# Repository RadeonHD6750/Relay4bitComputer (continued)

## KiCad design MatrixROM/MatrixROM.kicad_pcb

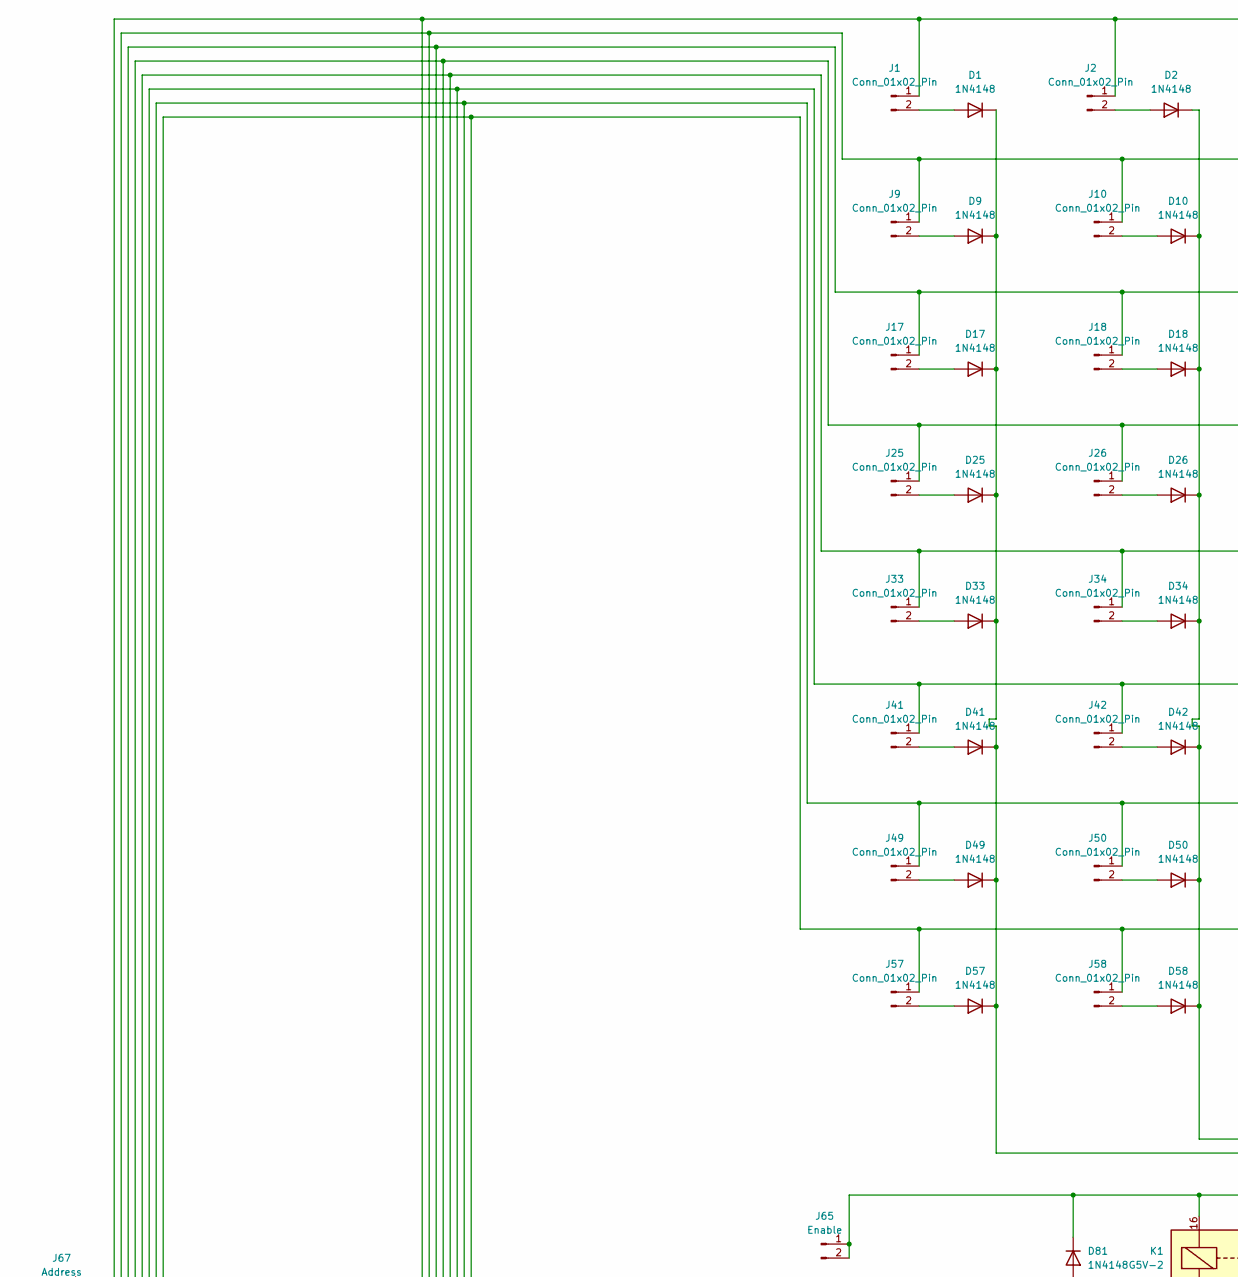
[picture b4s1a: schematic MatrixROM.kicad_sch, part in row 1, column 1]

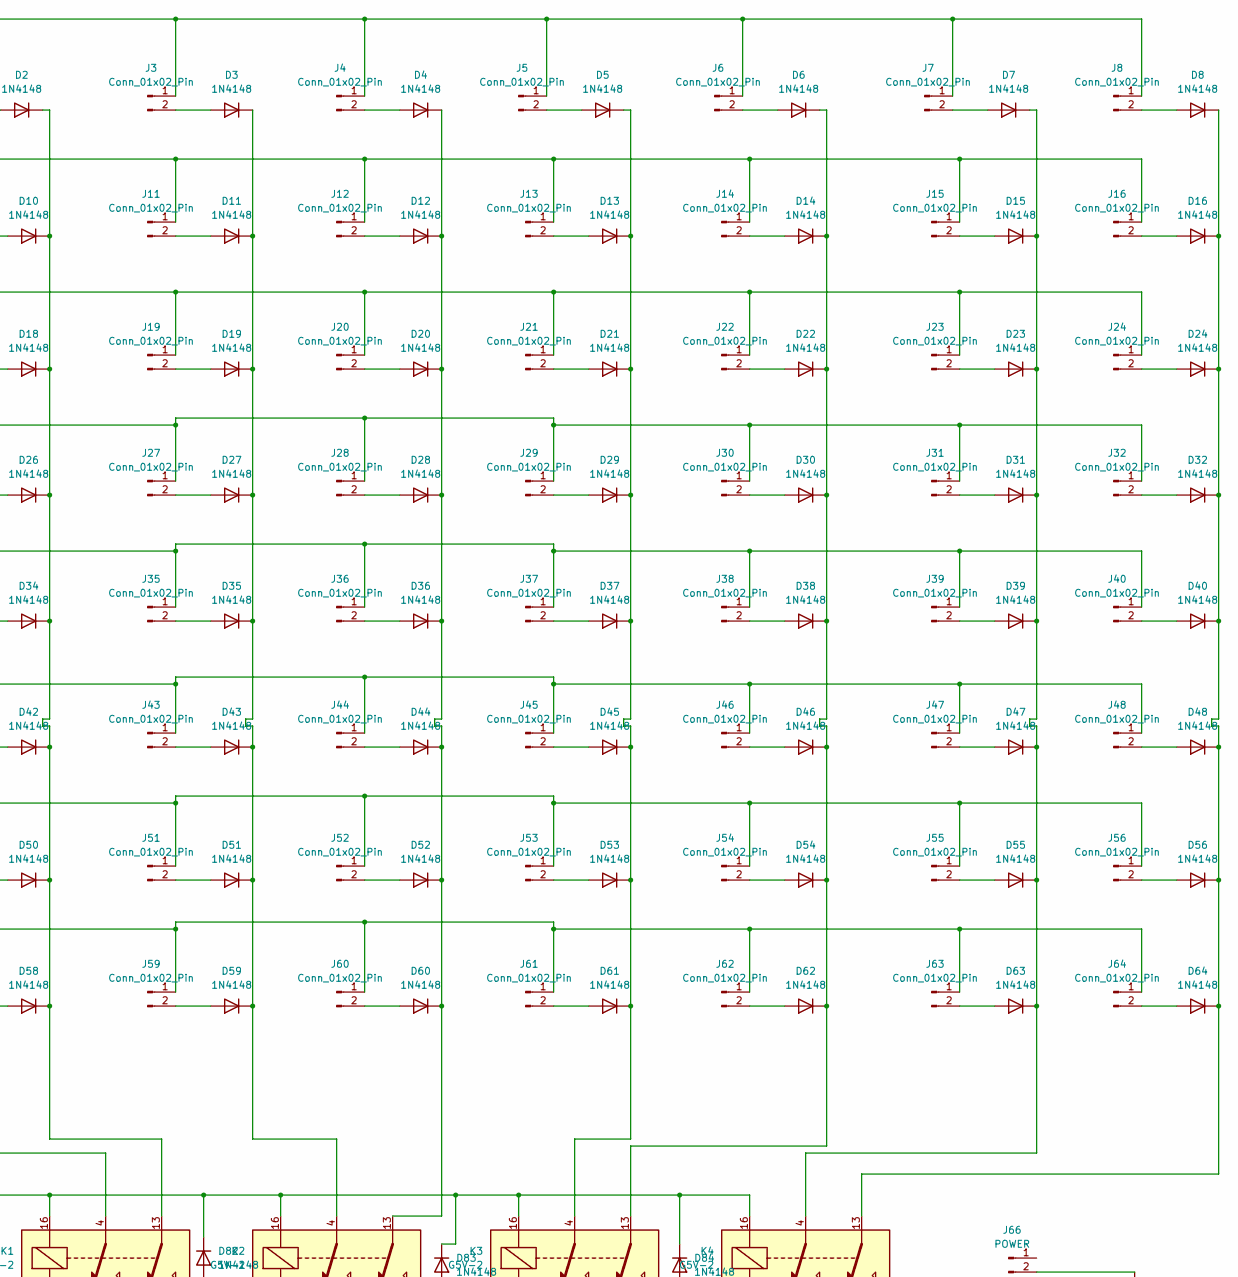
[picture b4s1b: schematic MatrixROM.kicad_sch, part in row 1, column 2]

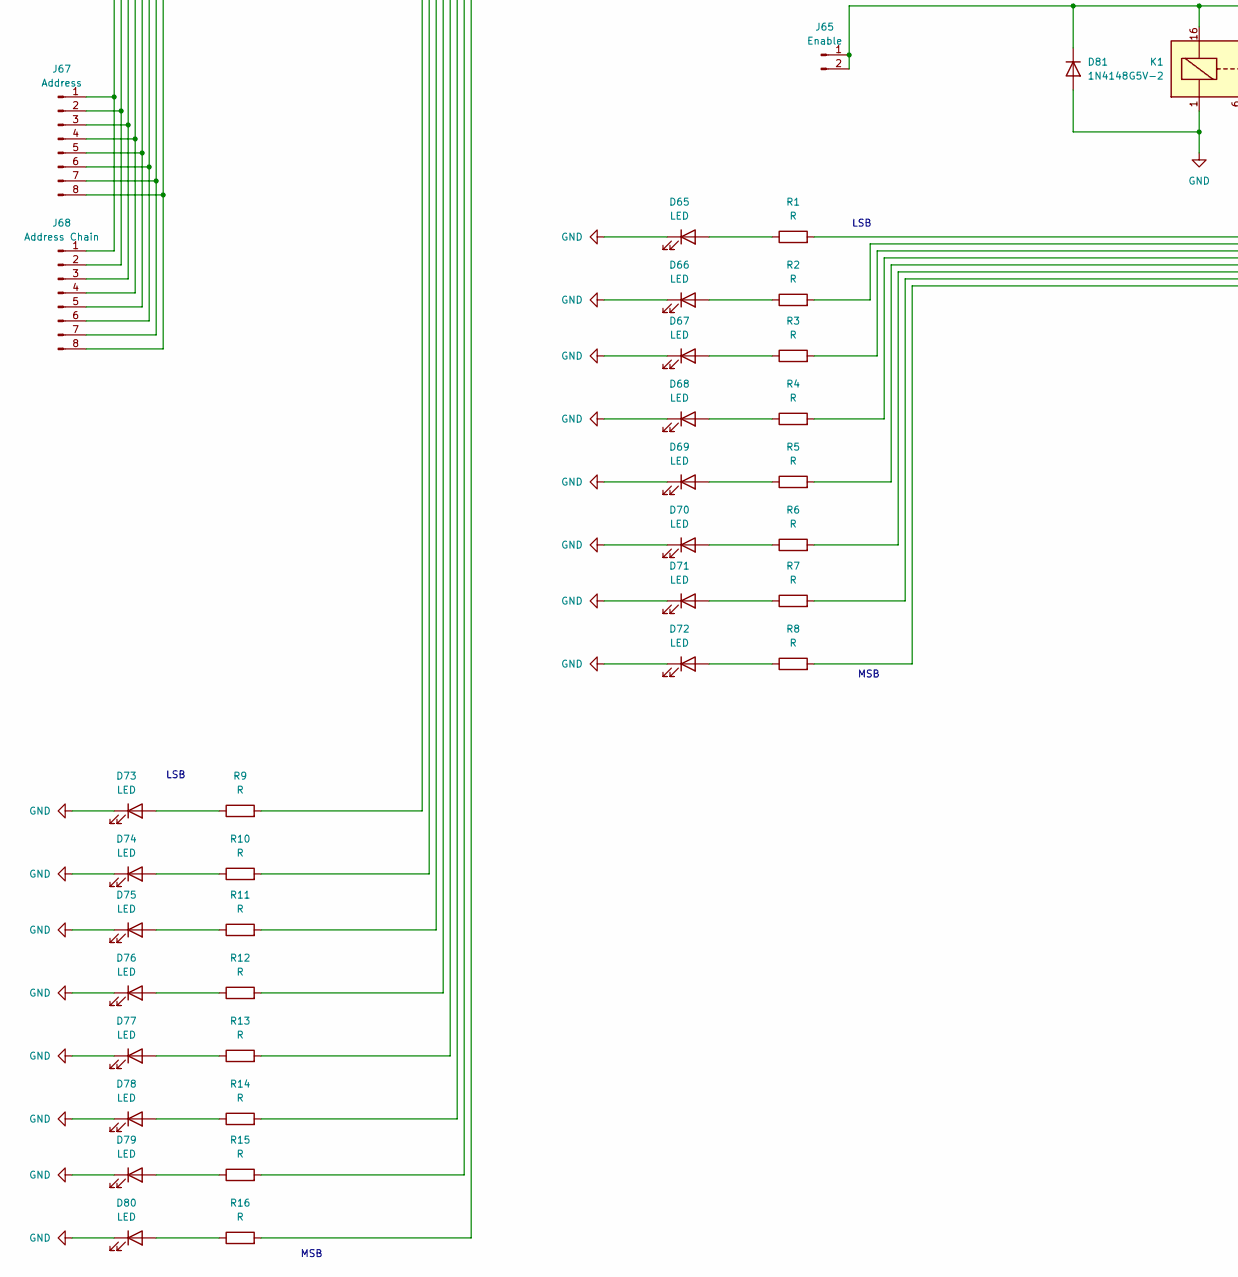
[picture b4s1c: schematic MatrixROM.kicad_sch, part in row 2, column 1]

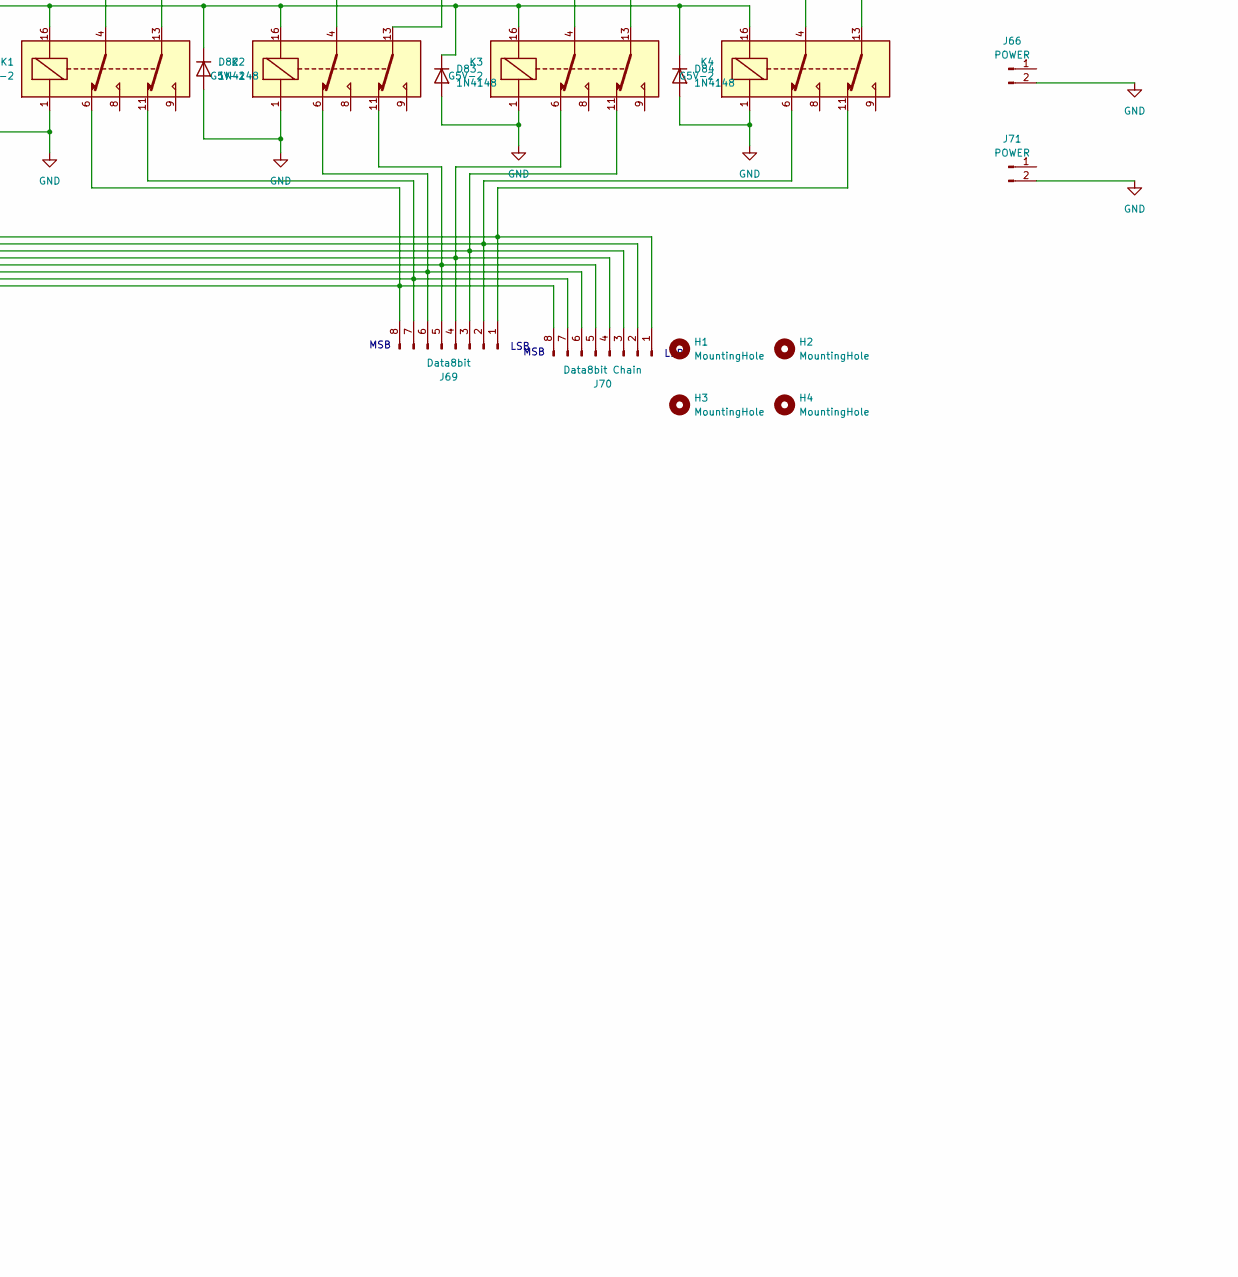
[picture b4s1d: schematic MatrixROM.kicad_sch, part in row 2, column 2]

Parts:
D1, D2, D3, D4, D5, D6, D7, D8, D9, D10, D11, D12, D13, D14, D15, D16, D17, D18, D19, D20, D21, D22, D23, D24, D25, D26, D27, D28, D29, D30, D31, D32, D33, D34, D35, D36, D37, D38, D39, D40, D41, D42, D43, D44, D45, D46, D47, D48, D49, D50, D51, D52, D53, D54, D55, D56, D57, D58, D59, D60, D61, D62, D63, D64, D81, D82, D83, D84: 1N4148; D_DO-35_SOD27_P7.62mm_Horizontal
D65, D66, D67, D68, D69, D70, D71, D72, D73, D74, D75, D76, D77, D78, D79, D80: LED; LED_D5.0mm
H1, H2, H3, H4: MountingHole; MountingHole_3.2mm_M3_Pad
J1, J2, J3, J4, J5, J6, J7, J8, J9, J10, J11, J12, J13, J14, J15, J16, J17, J18, J19, J20, J21, J22, J23, J24, J25, J26, J27, J28, J29, J30, J31, J32, J33, J34, J35, J36, J37, J38, J39, J40, J41, J42, J43, J44, J45, J46, J47, J48, J49, J50, J51, J52, J53, J54, J55, J56, J57, J58, J59, J60, J61, J62, J63, J64: Conn_01x02_Pin; PinHeader_1x02_P2.54mm_Vertical
J65: Enable; PinHeader_1x02_P2.54mm_Vertical
J66, J71: POWER; PinHeader_1x02_P2.54mm_Vertical
J67: Address; PinHeader_1x08_P2.54mm_Vertical
J68: Address Chain; PinHeader_1x08_P2.54mm_Vertical
J69: Data8bit; PinHeader_1x08_P2.54mm_Vertical
J70: Data8bit Chain; PinHeader_1x08_P2.54mm_Vertical
K1, K2, K3, K4: G5V-2; Relay_DPDT_Omron_G5V-2
R1, R2, R3, R4, R5, R6, R7, R8, R9, R10, R11, R12, R13, R14, R15, R16: R; R_Axial_DIN0207_L6.3mm_D2.5mm_P10.16mm_Horizontal

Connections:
GND: D65.1 (K), D66.1 (K), D67.1 (K), D68.1 (K), D69.1 (K), D70.1 (K), D71.1 (K), D72.1 (K), D73.1 (K), D74.1 (K), D75.1 (K), D76.1 (K), D77.1 (K), D78.1 (K), D79.1 (K), D80.1 (K), D81.2 (A), D82.2 (A), D83.2 (A), D84.2 (A), J66.2, J71.2, K1.1, K2.1, K3.1, K4.1
unnamed: D1.2 (A), J1.2
unnamed: D1.1 (K), D9.1 (K), D17.1 (K), D25.1 (K), D33.1 (K), D41.1 (K), D49.1 (K), D57.1 (K), K1.4
unnamed: D2.2 (A), J2.2
unnamed: D3.2 (A), J3.2
unnamed: D4.2 (A), J4.2
unnamed: D5.2 (A), J5.2
unnamed: D6.2 (A), J6.2
unnamed: D7.2 (A), J7.2
unnamed: D8.2 (A), J8.2
unnamed: D9.2 (A), J9.2
unnamed: D10.2 (A), J10.2
unnamed: D2.1 (K), D10.1 (K), D18.1 (K), D26.1 (K), D34.1 (K), D42.1 (K), D50.1 (K), D58.1 (K), K1.13
unnamed: D11.2 (A), J11.2
unnamed: D3.1 (K), D11.1 (K), D19.1 (K), D27.1 (K), D35.1 (K), D43.1 (K), D51.1 (K), D59.1 (K), K2.4
unnamed: D12.2 (A), J12.2
unnamed: D4.1 (K), D12.1 (K), D20.1 (K), D28.1 (K), D36.1 (K), D44.1 (K), D52.1 (K), D60.1 (K), K2.13
unnamed: D13.2 (A), J13.2
unnamed: D5.1 (K), D13.1 (K), D21.1 (K), D29.1 (K), D37.1 (K), D45.1 (K), D53.1 (K), D61.1 (K), K3.4
unnamed: D14.2 (A), J14.2
unnamed: D6.1 (K), D14.1 (K), D22.1 (K), D30.1 (K), D38.1 (K), D46.1 (K), D54.1 (K), D62.1 (K), K3.13
unnamed: D15.2 (A), J15.2
unnamed: D7.1 (K), D15.1 (K), D23.1 (K), D31.1 (K), D39.1 (K), D47.1 (K), D55.1 (K), D63.1 (K), K4.4
unnamed: D16.2 (A), J16.2
unnamed: D8.1 (K), D16.1 (K), D24.1 (K), D32.1 (K), D40.1 (K), D48.1 (K), D56.1 (K), D64.1 (K), K4.13
unnamed: D17.2 (A), J17.2
unnamed: D18.2 (A), J18.2
unnamed: D19.2 (A), J19.2
unnamed: D20.2 (A), J20.2
unnamed: D21.2 (A), J21.2
unnamed: D22.2 (A), J22.2
unnamed: D23.2 (A), J23.2
unnamed: D24.2 (A), J24.2
unnamed: D25.2 (A), J25.2
unnamed: D26.2 (A), J26.2
unnamed: D27.2 (A), J27.2
unnamed: D28.2 (A), J28.2
unnamed: D29.2 (A), J29.2
unnamed: D30.2 (A), J30.2
unnamed: D31.2 (A), J31.2
unnamed: D32.2 (A), J32.2
unnamed: D33.2 (A), J33.2
unnamed: D34.2 (A), J34.2
unnamed: D35.2 (A), J35.2
unnamed: D36.2 (A), J36.2
unnamed: D37.2 (A), J37.2
unnamed: D38.2 (A), J38.2
unnamed: D39.2 (A), J39.2
unnamed: D40.2 (A), J40.2
unnamed: D41.2 (A), J41.2
unnamed: D42.2 (A), J42.2
unnamed: D43.2 (A), J43.2
unnamed: D44.2 (A), J44.2
unnamed: D45.2 (A), J45.2
unnamed: D46.2 (A), J46.2
unnamed: D47.2 (A), J47.2
unnamed: D48.2 (A), J48.2
unnamed: D49.2 (A), J49.2
unnamed: D50.2 (A), J50.2
unnamed: D51.2 (A), J51.2
unnamed: D52.2 (A), J52.2
unnamed: D53.2 (A), J53.2
unnamed: D54.2 (A), J54.2
unnamed: D55.2 (A), J55.2
unnamed: D56.2 (A), J56.2
unnamed: D57.2 (A), J57.2
unnamed: D58.2 (A), J58.2
unnamed: D59.2 (A), J59.2
unnamed: D60.2 (A), J60.2
unnamed: D61.2 (A), J61.2
unnamed: D62.2 (A), J62.2
unnamed: D63.2 (A), J63.2
unnamed: D64.2 (A), J64.2
unnamed: D65.2 (A), R1.1
unnamed: D66.2 (A), R2.1
unnamed: D67.2 (A), R3.1
unnamed: D68.2 (A), R4.1
unnamed: D69.2 (A), R5.1
unnamed: D70.2 (A), R6.1
unnamed: D71.2 (A), R7.1
unnamed: D72.2 (A), R8.1
unnamed: D73.2 (A), R9.1
unnamed: D74.2 (A), R10.1
unnamed: D75.2 (A), R11.1
unnamed: D76.2 (A), R12.1
unnamed: D77.2 (A), R13.1
unnamed: D78.2 (A), R14.1
unnamed: D79.2 (A), R15.1
unnamed: D80.2 (A), R16.1
unnamed: D81.1 (K), D82.1 (K), D83.1 (K), D84.1 (K), J65.1, J65.2, K1.16, K2.16, K3.16, K4.16
unnamed: J1.1, J2.1, J3.1, J4.1, J5.1, J6.1, J7.1, J8.1, J67.1, J68.1, R9.2
unnamed: J9.1, J10.1, J11.1, J12.1, J13.1, J14.1, J15.1, J16.1, J67.2, J68.2, R10.2
unnamed: J17.1, J18.1, J19.1, J20.1, J21.1, J22.1, J23.1, J24.1, J67.3, J68.3, R11.2
unnamed: J25.1, J26.1, J27.1, J28.1, J29.1, J30.1, J31.1, J32.1, J67.4, J68.4, R12.2
unnamed: J33.1, J34.1, J35.1, J36.1, J37.1, J38.1, J39.1, J40.1, J67.5, J68.5, R13.2
unnamed: J41.1, J42.1, J43.1, J44.1, J45.1, J46.1, J47.1, J48.1, J67.6, J68.6, R14.2
unnamed: J49.1, J50.1, J51.1, J52.1, J53.1, J54.1, J55.1, J56.1, J67.7, J68.7, R15.2
unnamed: J57.1, J58.1, J59.1, J60.1, J61.1, J62.1, J63.1, J64.1, J67.8, J68.8, R16.2
unnamed: J69.1, J70.1, K4.11, R1.2
unnamed: J69.2, J70.2, K4.6, R2.2
unnamed: J69.3, J70.3, K3.11, R3.2
unnamed: J69.4, J70.4, K3.6, R4.2
unnamed: J69.5, J70.5, K2.11, R5.2
unnamed: J69.6, J70.6, K2.6, R6.2
unnamed: J69.7, J70.7, K1.11, R7.2
unnamed: J69.8, J70.8, K1.6, R8.2

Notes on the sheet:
MSB
LSB

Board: 2 copper layers, 179 parts (16 on the bottom side), 106 nets, no tracks yet.

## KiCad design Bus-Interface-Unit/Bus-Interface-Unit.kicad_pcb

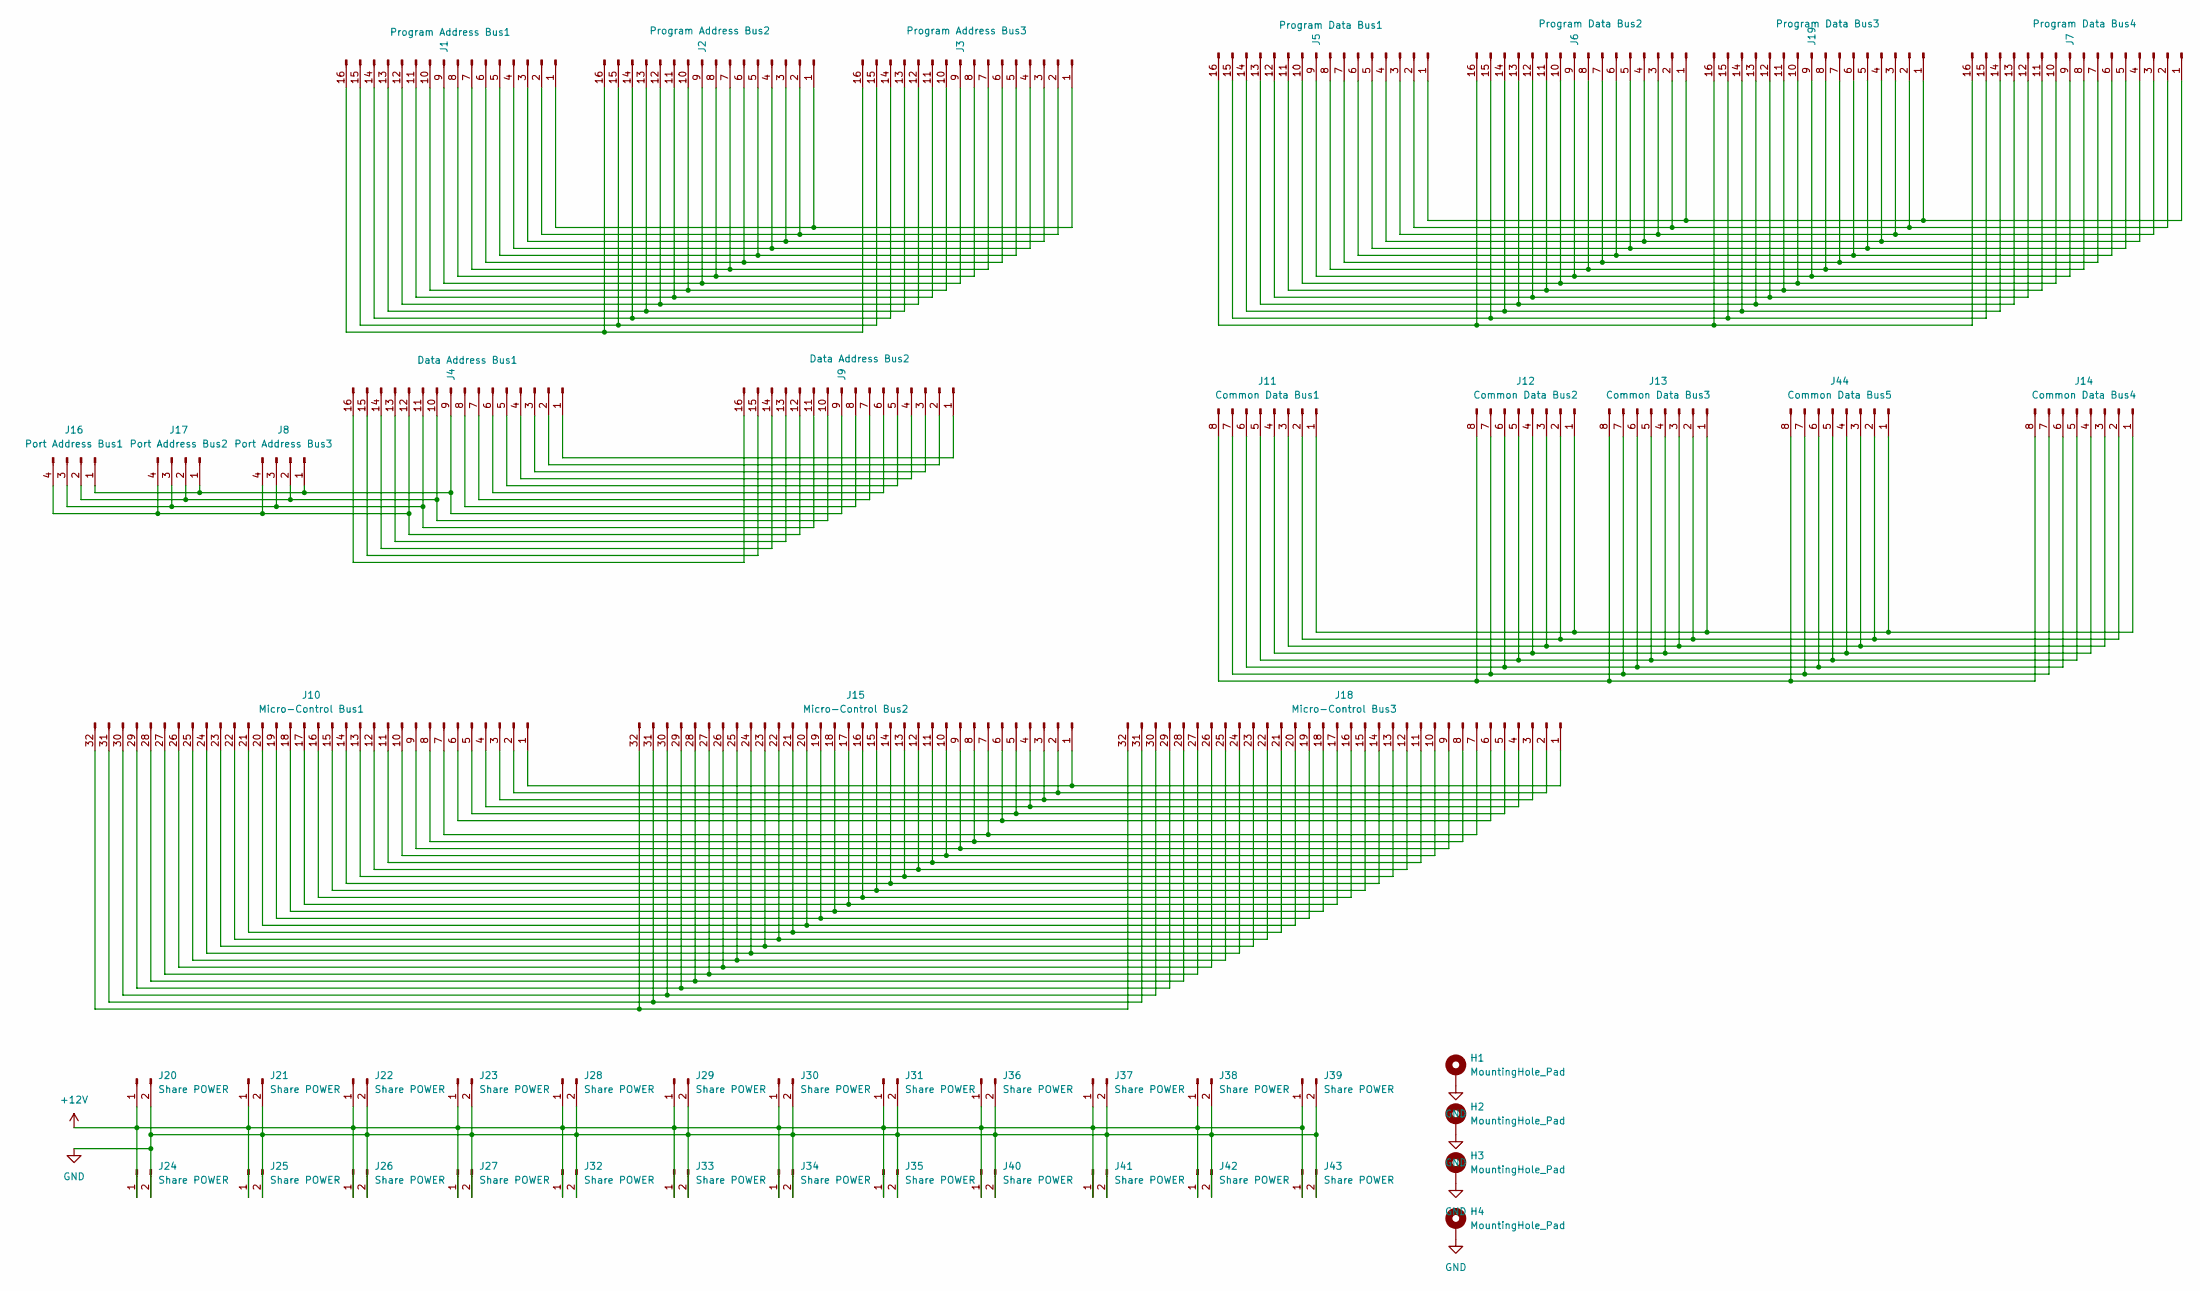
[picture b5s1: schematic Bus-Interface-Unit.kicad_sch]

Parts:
H1, H2, H3, H4: MountingHole_Pad; MountingHole_3.2mm_M3_Pad
J1: Program Address Bus1; PinHeader_1x16_P2.54mm_Vertical
J2: Program Address Bus2; PinHeader_1x16_P2.54mm_Vertical
J3: Program Address Bus3; PinHeader_1x16_P2.54mm_Vertical
J4: Data Address Bus1; PinHeader_1x16_P2.54mm_Vertical
J5: Program Data Bus1; PinHeader_1x16_P2.54mm_Vertical
J6: Program Data Bus2; PinHeader_1x16_P2.54mm_Vertical
J7: Program Data Bus4; PinHeader_1x16_P2.54mm_Vertical
J8: Port Address Bus3; PinHeader_1x04_P2.54mm_Vertical
J9: Data Address Bus2; PinHeader_1x16_P2.54mm_Vertical
J10: Micro-Control Bus1; PinHeader_1x32_P2.54mm_Vertical
J11: Common Data Bus1; PinHeader_1x08_P2.54mm_Vertical
J12: Common Data Bus2; PinHeader_1x08_P2.54mm_Vertical
J13: Common Data Bus3; PinHeader_1x08_P2.54mm_Vertical
J14: Common Data Bus4; PinHeader_1x08_P2.54mm_Vertical
J15: Micro-Control Bus2; PinHeader_1x32_P2.54mm_Vertical
J16: Port Address Bus1; PinHeader_1x04_P2.54mm_Vertical
J17: Port Address Bus2; PinHeader_1x04_P2.54mm_Vertical
J18: Micro-Control Bus3; PinHeader_1x32_P2.54mm_Vertical
J19: Program Data Bus3; PinHeader_1x16_P2.54mm_Vertical
J20, J21, J22, J23, J24, J25, J26, J27, J28, J29, J30, J31, J32, J33, J34, J35, J36, J37, J38, J39, J40, J41, J42, J43: Share POWER; PinHeader_1x02_P2.54mm_Vertical
J44: Common Data Bus5; PinHeader_1x08_P2.54mm_Vertical

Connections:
+12V: J20.1, J21.1, J22.1, J23.1, J24.1, J25.1, J26.1, J27.1, J28.1, J29.1, J30.1, J31.1, J32.1, J33.1, J34.1, J35.1, J36.1, J37.1, J38.1, J39.1, J40.1, J41.1, J42.1, J43.1
GND: H1.1, H2.1, H3.1, H4.1, J20.2, J21.2, J22.2, J23.2, J24.2, J25.2, J26.2, J27.2, J28.2, J29.2, J30.2, J31.2, J32.2, J33.2, J34.2, J35.2, J36.2, J37.2, J38.2, J39.2, J40.2, J41.2, J42.2, J43.2
unnamed: J1.1, J2.1, J3.1
unnamed: J1.2, J2.2, J3.2
unnamed: J1.3, J2.3, J3.3
unnamed: J1.4, J2.4, J3.4
unnamed: J1.5, J2.5, J3.5
unnamed: J1.6, J2.6, J3.6
unnamed: J1.7, J2.7, J3.7
unnamed: J1.8, J2.8, J3.8
unnamed: J1.9, J2.9, J3.9
unnamed: J1.10, J2.10, J3.10
unnamed: J1.11, J2.11, J3.11
unnamed: J1.12, J2.12, J3.12
unnamed: J1.13, J2.13, J3.13
unnamed: J1.14, J2.14, J3.14
unnamed: J1.15, J2.15, J3.15
unnamed: J1.16, J2.16, J3.16
unnamed: J4.1, J9.1
unnamed: J4.2, J9.2
unnamed: J4.3, J9.3
unnamed: J4.4, J9.4
unnamed: J4.5, J9.5
unnamed: J4.6, J9.6
unnamed: J4.7, J9.7
unnamed: J4.8, J9.8
unnamed: J4.13, J9.13
unnamed: J4.14, J9.14
unnamed: J4.15, J9.15
unnamed: J4.16, J9.16
unnamed: J10.1, J15.1, J18.1
unnamed: J10.2, J15.2, J18.2
unnamed: J10.3, J15.3, J18.3
unnamed: J10.4, J15.4, J18.4
unnamed: J10.5, J15.5, J18.5
unnamed: J10.6, J15.6, J18.6
unnamed: J10.7, J15.7, J18.7
unnamed: J10.8, J15.8, J18.8
unnamed: J10.9, J15.9, J18.9
unnamed: J10.10, J15.10, J18.10
unnamed: J10.11, J15.11, J18.11
unnamed: J10.12, J15.12, J18.12
unnamed: J10.13, J15.13, J18.13
unnamed: J10.14, J15.14, J18.14
unnamed: J10.15, J15.15, J18.15
unnamed: J10.16, J15.16, J18.16
unnamed: J10.17, J15.17, J18.17
unnamed: J10.18, J15.18, J18.18
unnamed: J10.19, J15.19, J18.19
unnamed: J10.20, J15.20, J18.20
unnamed: J10.21, J15.21, J18.21
unnamed: J10.22, J15.22, J18.22
unnamed: J10.23, J15.23, J18.23
unnamed: J10.24, J15.24, J18.24
unnamed: J10.25, J15.25, J18.25
unnamed: J10.26, J15.26, J18.26
unnamed: J10.27, J15.27, J18.27
unnamed: J10.28, J15.28, J18.28
unnamed: J10.29, J15.29, J18.29
unnamed: J10.30, J15.30, J18.30
unnamed: J10.31, J15.31, J18.31
unnamed: J10.32, J15.32, J18.32
unnamed: J11.1, J12.1, J13.1, J14.1, J44.1
unnamed: J11.2, J12.2, J13.2, J14.2, J44.2
unnamed: J11.3, J12.3, J13.3, J14.3, J44.3
unnamed: J11.4, J12.4, J13.4, J14.4, J44.4
unnamed: J11.5, J12.5, J13.5, J14.5, J44.5
unnamed: J11.6, J12.6, J13.6, J14.6, J44.6
unnamed: J11.7, J12.7, J13.7, J14.7, J44.7
unnamed: J11.8, J12.8, J13.8, J14.8, J44.8
unnamed: J4.9, J8.1, J9.9, J16.1, J17.1
unnamed: J4.10, J8.2, J9.10, J16.2, J17.2
unnamed: J4.11, J8.3, J9.11, J16.3, J17.3
unnamed: J4.12, J8.4, J9.12, J16.4, J17.4
unnamed: J5.1, J6.1, J7.1, J19.1
unnamed: J5.2, J6.2, J7.2, J19.2
unnamed: J5.3, J6.3, J7.3, J19.3
unnamed: J5.4, J6.4, J7.4, J19.4
unnamed: J5.5, J6.5, J7.5, J19.5
unnamed: J5.6, J6.6, J7.6, J19.6
unnamed: J5.7, J6.7, J7.7, J19.7
unnamed: J5.8, J6.8, J7.8, J19.8
unnamed: J5.9, J6.9, J7.9, J19.9
unnamed: J5.10, J6.10, J7.10, J19.10
unnamed: J5.11, J6.11, J7.11, J19.11
unnamed: J5.12, J6.12, J7.12, J19.12
unnamed: J5.13, J6.13, J7.13, J19.13
unnamed: J5.14, J6.14, J7.14, J19.14
unnamed: J5.15, J6.15, J7.15, J19.15
unnamed: J5.16, J6.16, J7.16, J19.16

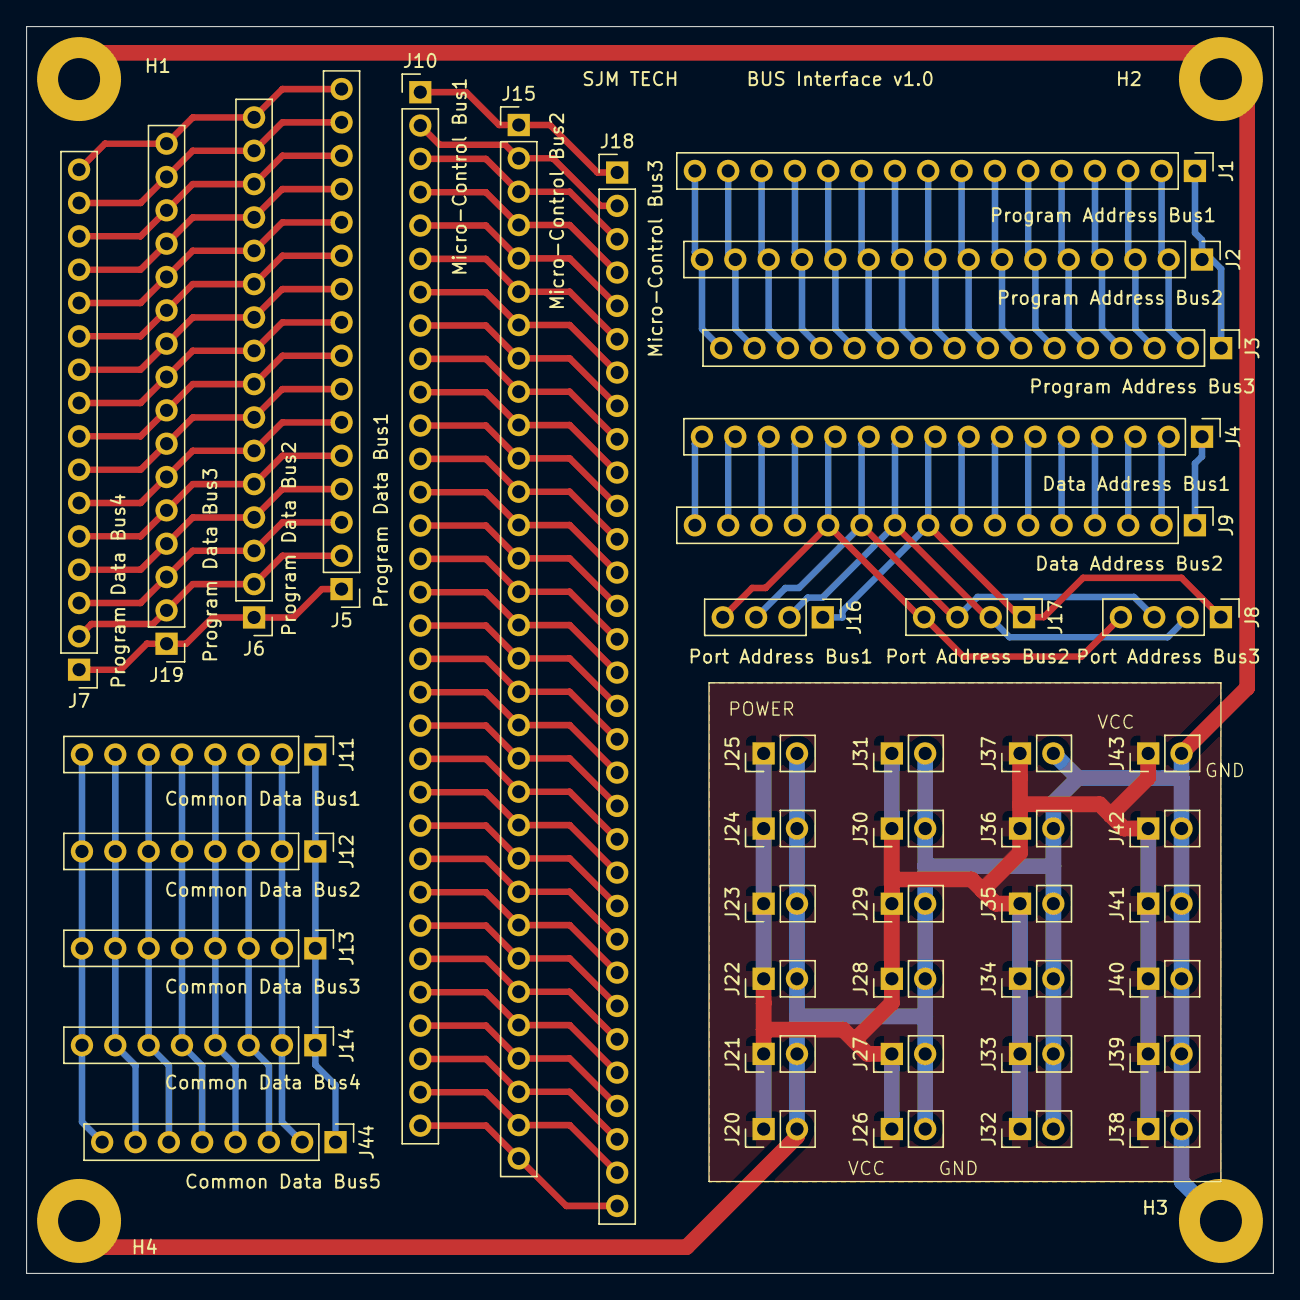
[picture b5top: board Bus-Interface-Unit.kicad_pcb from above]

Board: 2 copper layers, 95.0 x 95.0 mm, 48 parts (0 on the bottom side), 90 nets.

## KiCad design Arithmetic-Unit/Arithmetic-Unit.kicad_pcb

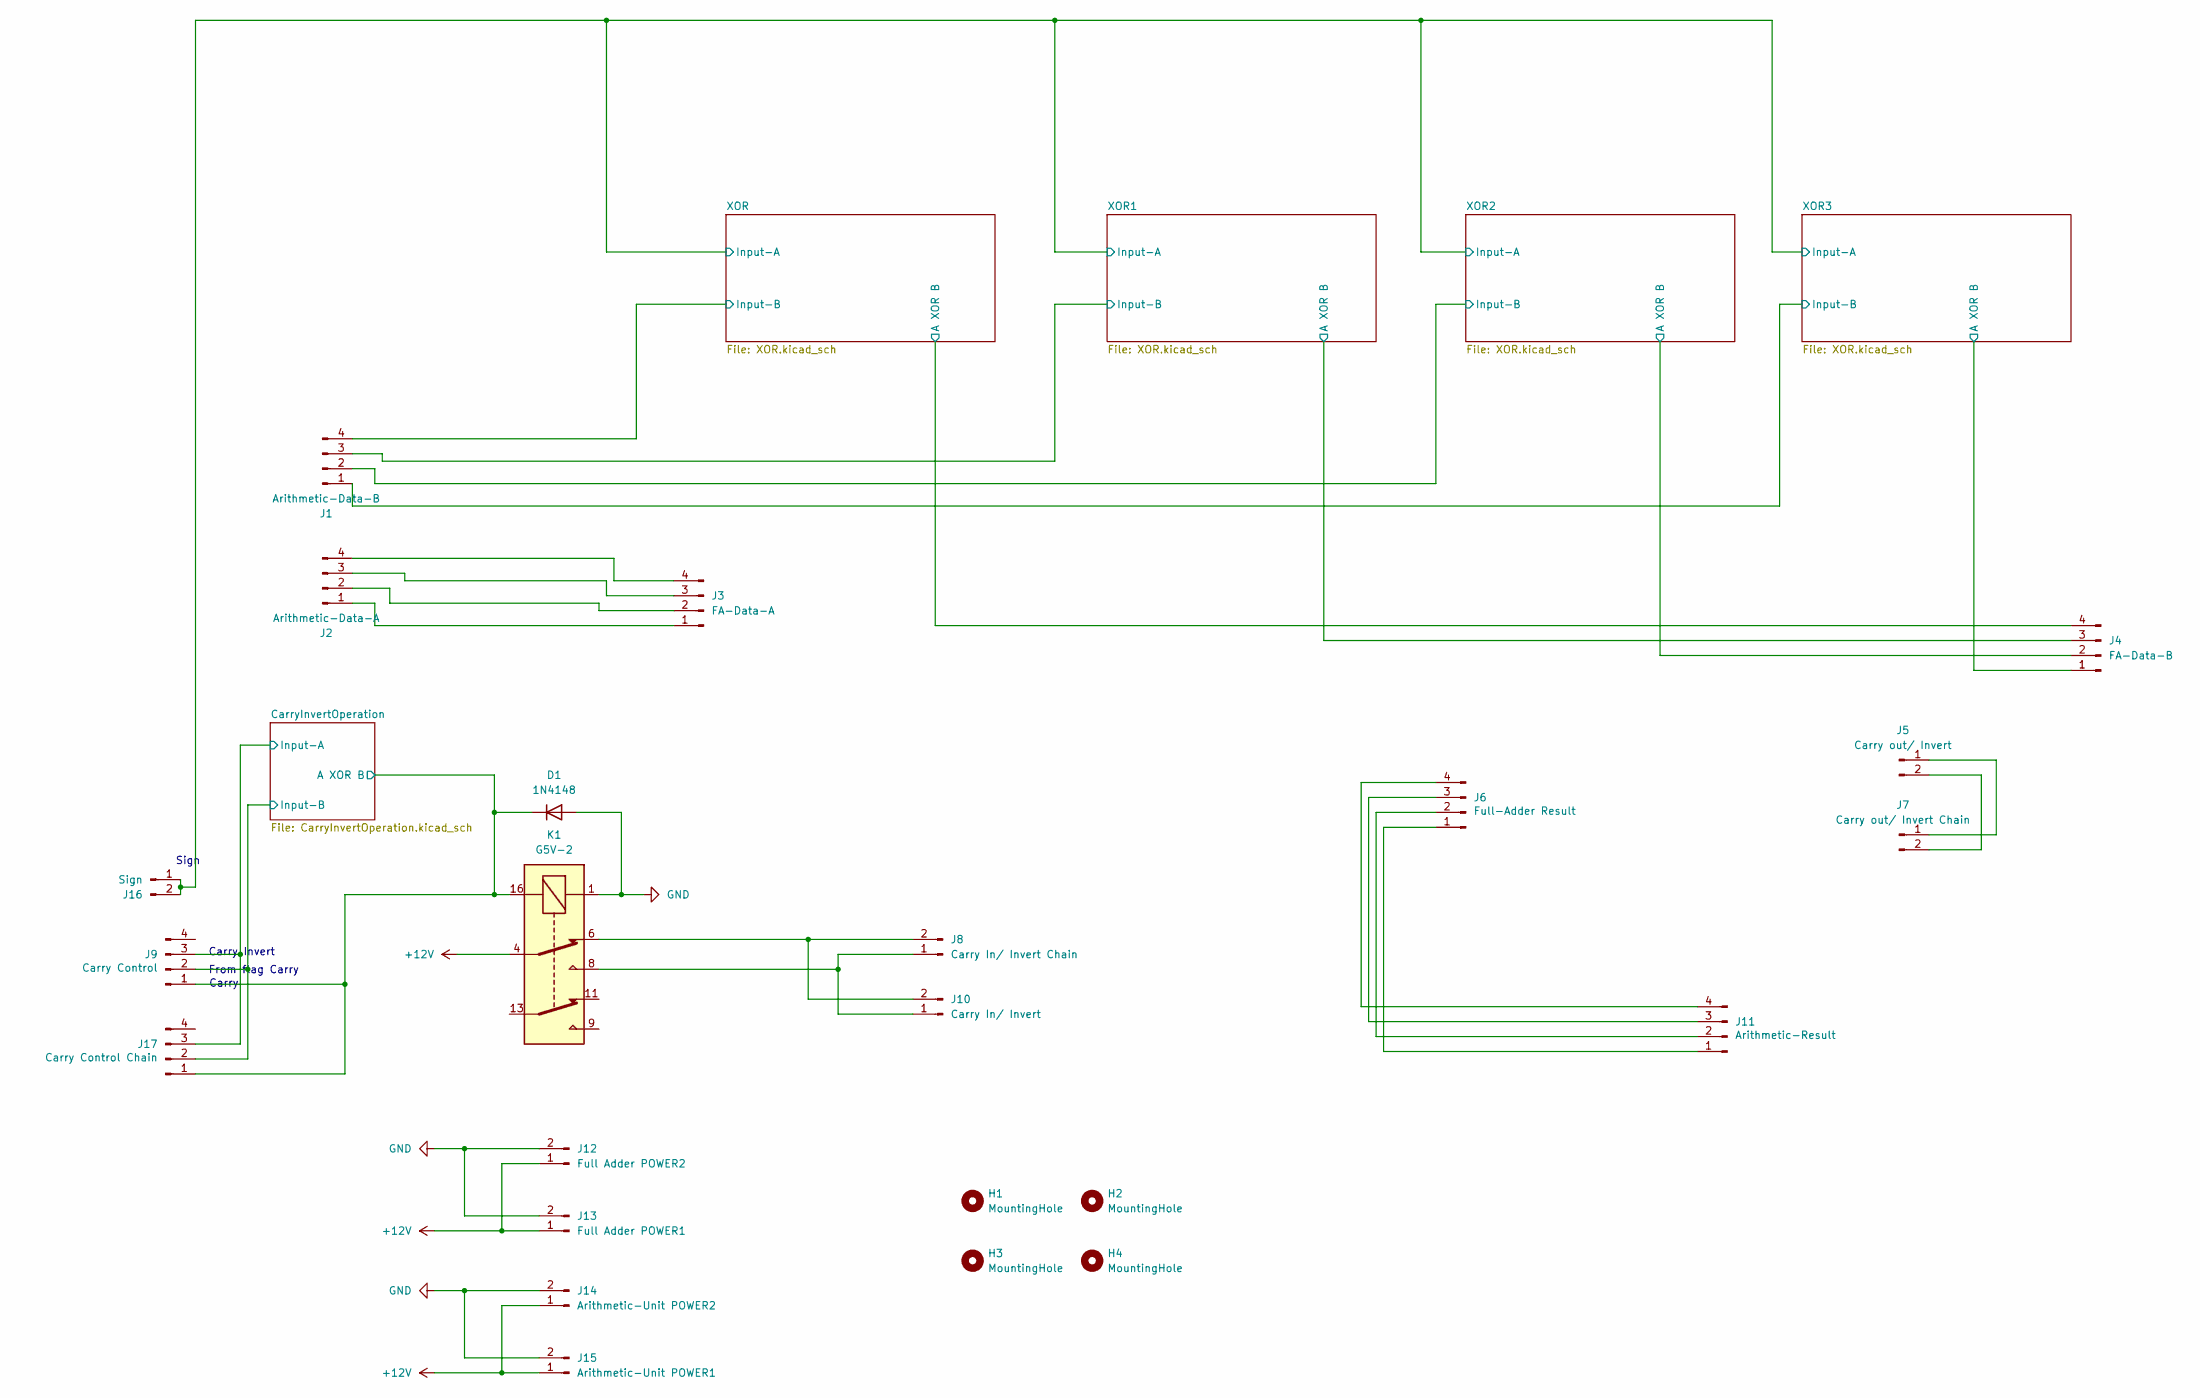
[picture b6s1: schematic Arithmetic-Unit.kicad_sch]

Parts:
D1: 1N4148; D_DO-35_SOD27_P7.62mm_Horizontal
H1, H2, H3, H4: MountingHole; MountingHole_3.2mm_M3_Pad
J1: Arithmetic-Data-B; PinHeader_1x04_P2.54mm_Vertical
J2: Arithmetic-Data-A; PinHeader_1x04_P2.54mm_Vertical
J3: FA-Data-A; PinHeader_1x04_P2.54mm_Vertical
J4: FA-Data-B; PinHeader_1x04_P2.54mm_Vertical
J5: Carry out/ Invert; PinHeader_1x02_P2.54mm_Vertical
J6: Full-Adder Result; PinHeader_1x04_P2.54mm_Vertical
J7: Carry out/ Invert Chain; PinHeader_1x02_P2.54mm_Vertical
J8: Carry In/ Invert Chain; PinHeader_1x02_P2.54mm_Vertical
J9: Carry Control; PinHeader_1x04_P2.54mm_Vertical
J10: Carry In/ Invert; PinHeader_1x02_P2.54mm_Vertical
J11: Arithmetic-Result; PinHeader_1x04_P2.54mm_Vertical
J12: Full Adder POWER2; PinHeader_1x02_P2.54mm_Vertical
J13: Full Adder POWER1; PinHeader_1x02_P2.54mm_Vertical
J14: Arithmetic-Unit POWER2; PinHeader_1x02_P2.54mm_Vertical
J15: Arithmetic-Unit POWER1; PinHeader_1x02_P2.54mm_Vertical
J16: Sign; PinHeader_1x02_P2.54mm_Vertical
J17: Carry Control Chain; PinHeader_1x04_P2.54mm_Vertical
K1: G5V-2; Relay_DPDT_Omron_G5V-2

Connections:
+12V: J12.1, J13.1, J14.1, J15.1, K1.4; also elsewhere on the board
/CarryInvertOperation/A XOR B: D1.1 (K), J9.1, J17.1, K1.16; also elsewhere on the board
/CarryInvertOperation/Input-A: J9.3, J17.3; also elsewhere on the board
/CarryInvertOperation/Input-B: J9.2, J17.2; also elsewhere on the board
/XOR1/A XOR B: J4.3; also elsewhere on the board
/XOR1/Input-B: J1.3; also elsewhere on the board
/XOR2/A XOR B: J4.2; also elsewhere on the board
/XOR2/Input-B: J1.2; also elsewhere on the board
/XOR3/A XOR B: J4.1; also elsewhere on the board
/XOR3/Input-B: J1.1; also elsewhere on the board
/XOR/A XOR B: J4.4; also elsewhere on the board
/XOR/Input-A: J16.1, J16.2; also elsewhere on the board
/XOR/Input-B: J1.4; also elsewhere on the board
GND: D1.2 (A), J12.2, J13.2, J14.2, J15.2, K1.1; also elsewhere on the board
unnamed: J2.1, J3.1
unnamed: J2.2, J3.2
unnamed: J2.3, J3.3
unnamed: J2.4, J3.4
unnamed: J5.1, J7.1
unnamed: J5.2, J7.2
unnamed: J8.1, J10.1, K1.8
unnamed: J8.2, J10.2, K1.6
unnamed: J6.1, J11.1
unnamed: J6.2, J11.2
unnamed: J6.3, J11.3
unnamed: J6.4, J11.4

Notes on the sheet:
From flag Carry
Carry Invert
Carry
Sign
